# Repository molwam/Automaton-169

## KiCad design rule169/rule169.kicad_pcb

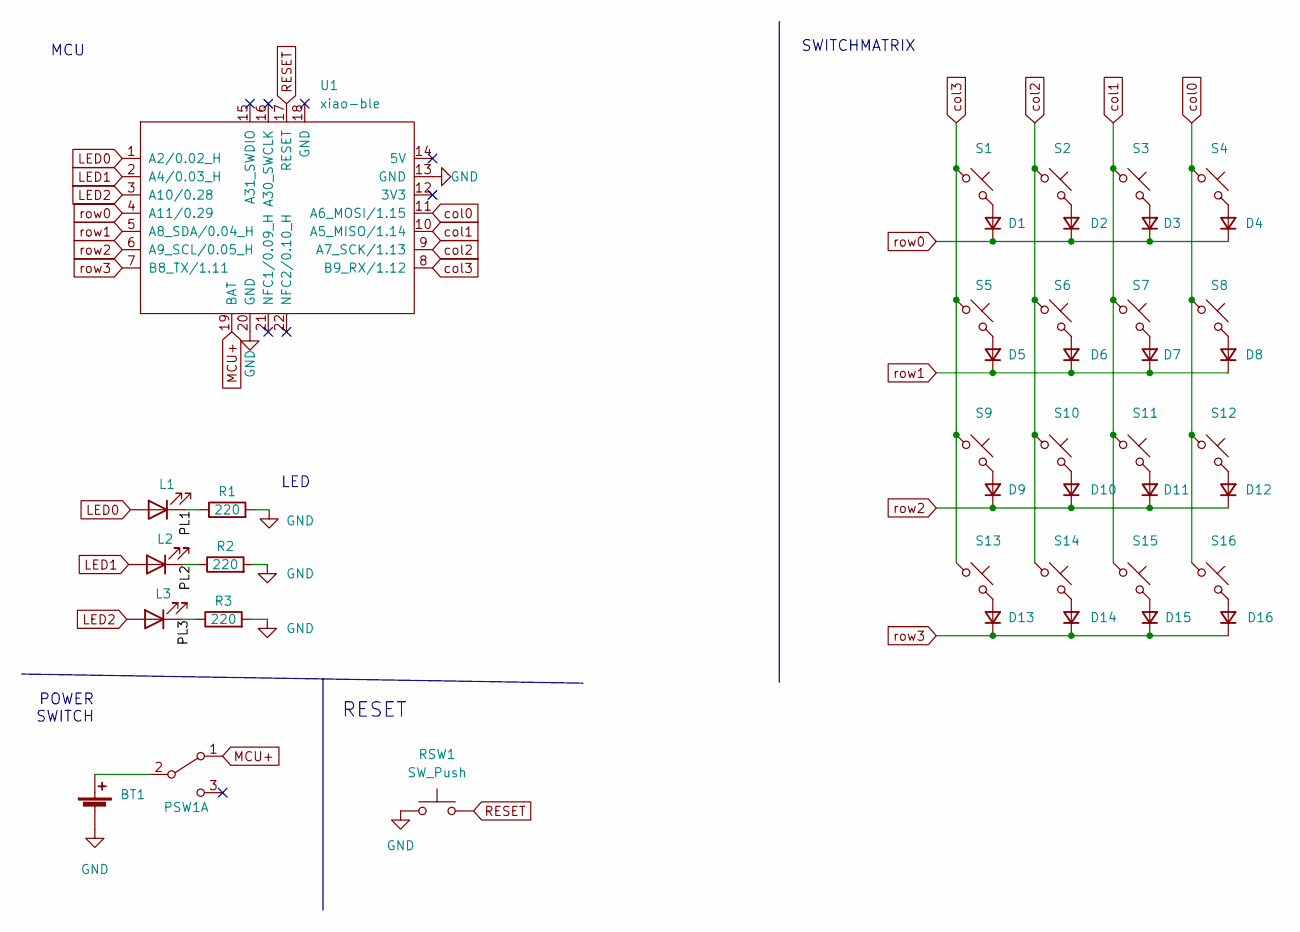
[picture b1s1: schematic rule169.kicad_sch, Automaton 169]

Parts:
BT1: Battery_Cell; JST_PH_reversible
D1, D2, D3, D4, D5, D6, D7, D8, D9, D10, D11, D12, D13, D14, D15, D16: D_Small; Diode_SOD123
L1, L2, L3: LED; LED_3mm_reversible
PSW1: SW_DPDT_x2; MSK12C02_reversible
R1, R2, R3: 220; R_1206_DoubleSided
RSW1: SW_Push; ResetSW
S1, S2, S3, S4, S5, S6, S7, S8, S9, S10, S11, S12, S13, S14, S15, S16: MX_SW_HS; Kailh_socket_PG1350_optional_reversible
U1: xiao-ble; xiao seed ble

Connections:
/PL1: L1.1 (K), R1.1
/PL2: L2.1 (K), R2.1
/PL3: L3.1 (K), R3.1
GND: BT1.2 (-), R1.2, R2.2, R3.2, RSW1.1, U1.13 (GND), U1.20 (GND)
LED0: L1.2 (A), U1.1 (A2/0.02_H)
LED1: L2.2 (A), U1.2 (A4/0.03_H)
LED2: L3.2 (A), U1.3 (A10/0.28)
MCU+: PSW1.1 (A), U1.19 (BAT)
unnamed: BT1.1 (+), PSW1.2 (B)
unnamed: D1.2 (A), S1.2
unnamed: D2.2 (A), S2.2
unnamed: D3.2 (A), S3.2
unnamed: D4.2 (A), S4.2
unnamed: D5.2 (A), S5.2
unnamed: D6.2 (A), S6.2
unnamed: D7.2 (A), S7.2
unnamed: D8.2 (A), S8.2
unnamed: D9.2 (A), S9.2
unnamed: D10.2 (A), S10.2
unnamed: D11.2 (A), S11.2
unnamed: D12.2 (A), S12.2
unnamed: D13.2 (A), S13.2
unnamed: D14.2 (A), S14.2
unnamed: D15.2 (A), S15.2
unnamed: D16.2 (A), S16.2
RESET: RSW1.2, U1.17 (RESET)
col0: S4.1, S8.1, S12.1, S16.1, U1.11 (A6_MOSI/1.15)
col1: S3.1, S7.1, S11.1, S15.1, U1.10 (A5_MISO/1.14)
col2: S2.1, S6.1, S10.1, S14.1, U1.9 (A7_SCK/1.13)
col3: S1.1, S5.1, S9.1, S13.1, U1.8 (B9_RX/1.12)
row0: D1.1 (K), D2.1 (K), D3.1 (K), D4.1 (K), U1.4 (A11/0.29)
row1: D5.1 (K), D6.1 (K), D7.1 (K), D8.1 (K), U1.5 (A8_SDA/0.04_H)
row2: D9.1 (K), D10.1 (K), D11.1 (K), D12.1 (K), U1.6 (A9_SCL/0.05_H)
row3: D13.1 (K), D14.1 (K), D15.1 (K), D16.1 (K), U1.7 (B8_TX/1.11)

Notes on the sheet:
RESET
POWER SWITCH
MCU
SWITCHMATRIX
LED

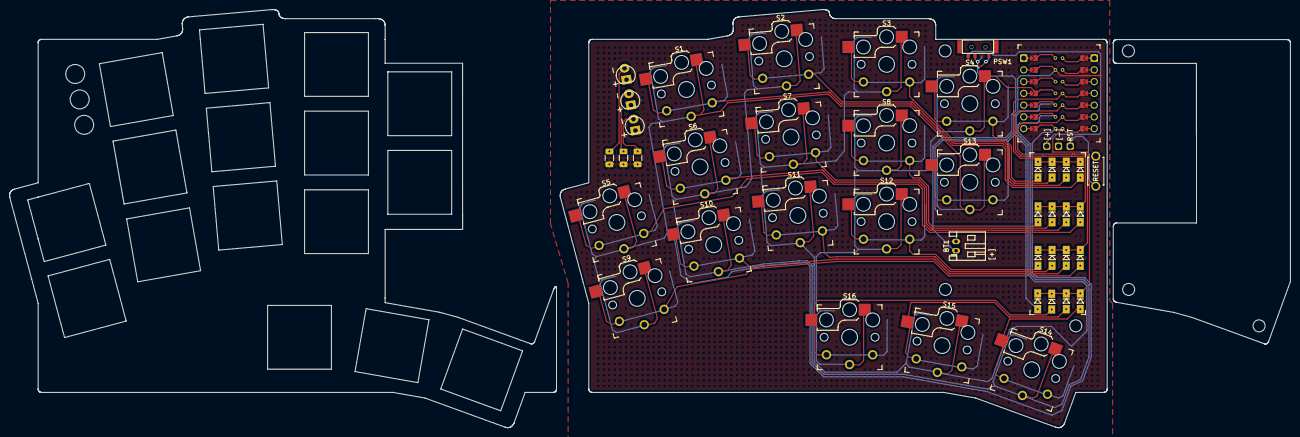
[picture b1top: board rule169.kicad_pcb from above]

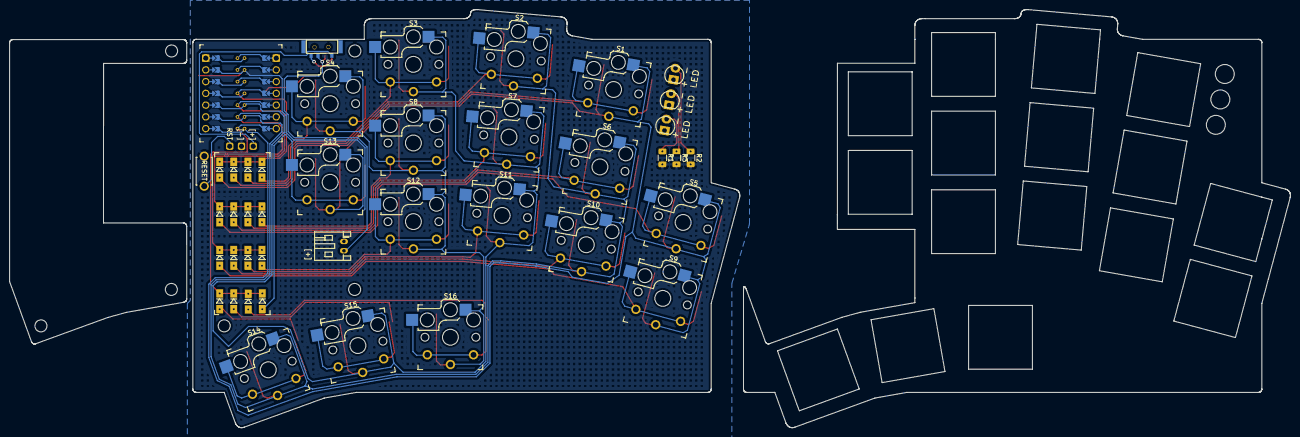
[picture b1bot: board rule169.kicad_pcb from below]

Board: 2 copper layers, 276.9 x 90.4 mm, 42 parts (3 on the bottom side), 34 nets.

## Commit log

2022-11-12 initialize repo
2022-12-19 add project files
2022-12-21 add silkscreen
2023-02-04 panelize pcbs
2023-02-04 cleanup
2023-02-04 add docs
2023-02-05 add links
